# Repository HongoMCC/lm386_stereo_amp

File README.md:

# LM386_Stereo_Amp

stereo audio amp using lm386

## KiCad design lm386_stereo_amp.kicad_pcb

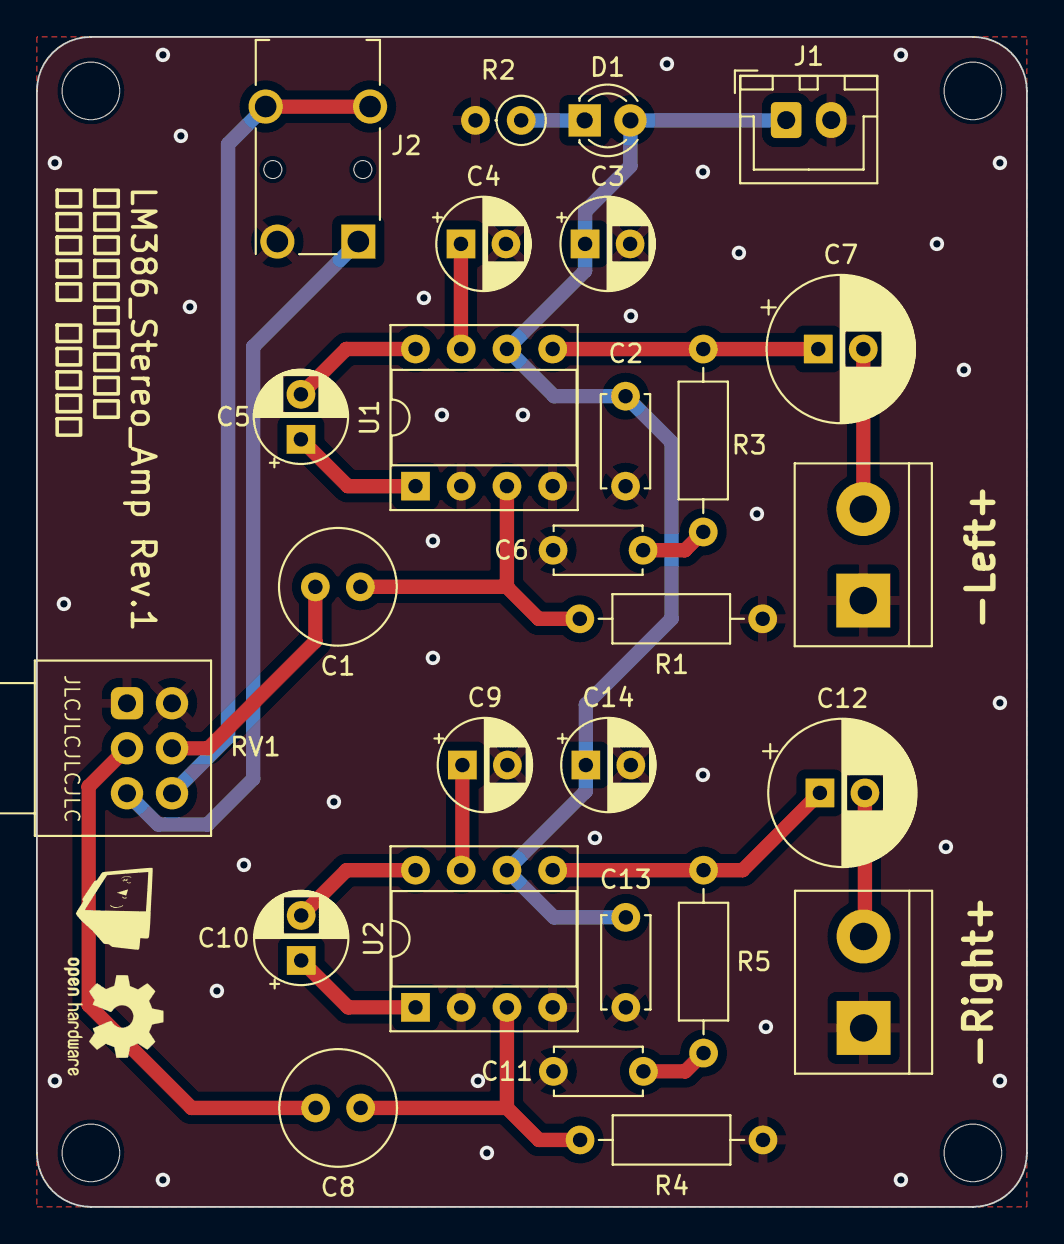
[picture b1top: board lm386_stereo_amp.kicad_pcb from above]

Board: 2 copper layers, 55.0 x 65.0 mm, 31 parts (0 on the bottom side), 21 nets.

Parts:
C1, C8: 4.7uF; C_Radial_D6.3mm_H5.0mm_P2.50mm
C2, C13: 0.1uF; C_Disc_D5.0mm_W2.5mm_P5.00mm
C3, C14: 100uF; CP_Radial_D5.0mm_P2.50mm
C4, C5, C9, C10: 10uF; CP_Radial_D5.0mm_P2.50mm
C6, C11: 0.047uF; C_Disc_D4.7mm_W2.5mm_P5.00mm
C7, C12: 470uF; CP_Radial_D8.0mm_P2.50mm
D1: LED_Small; LED_D3.0mm
H1, H2, H3, H4: MountingHole; MountingHole_3.2mm_M3
J1: Conn_01x02_Pin; JST_XH_B2B-XH-A_1x02_P2.50mm_Vertical
J2: AudioJack3; Jack_3.5mm_Switronic_ST-005-G_horizontal
J3, J4: Conn_01x02_Pin; TerminalBlock_bornier-2_P5.08mm
R1, R4: 10kΩ; R_Axial_DIN0207_L6.3mm_D2.5mm_P10.16mm_Horizontal
R2: 5.1kΩ; R_Axial_DIN0207_L6.3mm_D2.5mm_P2.54mm_Vertical
R3, R5: 10Ω; R_Axial_DIN0207_L6.3mm_D2.5mm_P10.16mm_Horizontal
RV1: R_Potentiometer_Dual; Potentiometer_Alps_RK097_Dual_Horizontal
U1, U2: LM386; DIP-8_W7.62mm_Socket

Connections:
+9V: C2.1, C3.1, C13.1, C14.1, D1.2 (A), J1.1, U1.6 (V+), U2.6 (V+)
GND: C2.2, C3.2, C4.2, C6.2, C9.2, C11.2, C13.2, C14.2, J1.2, J2.S, J3.1, J4.1, R1.2, R2.2, R4.2, RV1.1, RV1.4, U1.2 (-), U1.4 (GND), U2.2 (-), U2.4 (GND)
unnamed: C1.2, RV1.5
unnamed: C5.1, U1.1 (GAIN)
unnamed: C5.2, U1.8 (GAIN)
unnamed: C6.1, R3.1
unnamed: C7.1, R3.2, U1.5
unnamed: C8.2, RV1.2
unnamed: C10.1, U2.1 (GAIN)
unnamed: C10.2, U2.8 (GAIN)
unnamed: C11.1, R5.1
unnamed: C12.1, R5.2, U2.5
unnamed: D1.1 (K), R2.1
unnamed: J2.R, RV1.3
unnamed: J2.T, RV1.6
unnamed: C7.2, J3.2
unnamed: C12.2, J4.2
unnamed: C1.1, R1.1, U1.3 (+)
unnamed: C4.1, U1.7 (BYPASS)
unnamed: C8.1, R4.1, U2.3 (+)
unnamed: C9.1, U2.7 (BYPASS)

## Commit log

2024-08-03 init
2024-08-03 up to date
2024-08-09 place vias
2024-08-14 fix input wire
2024-08-19 generate gerber files
